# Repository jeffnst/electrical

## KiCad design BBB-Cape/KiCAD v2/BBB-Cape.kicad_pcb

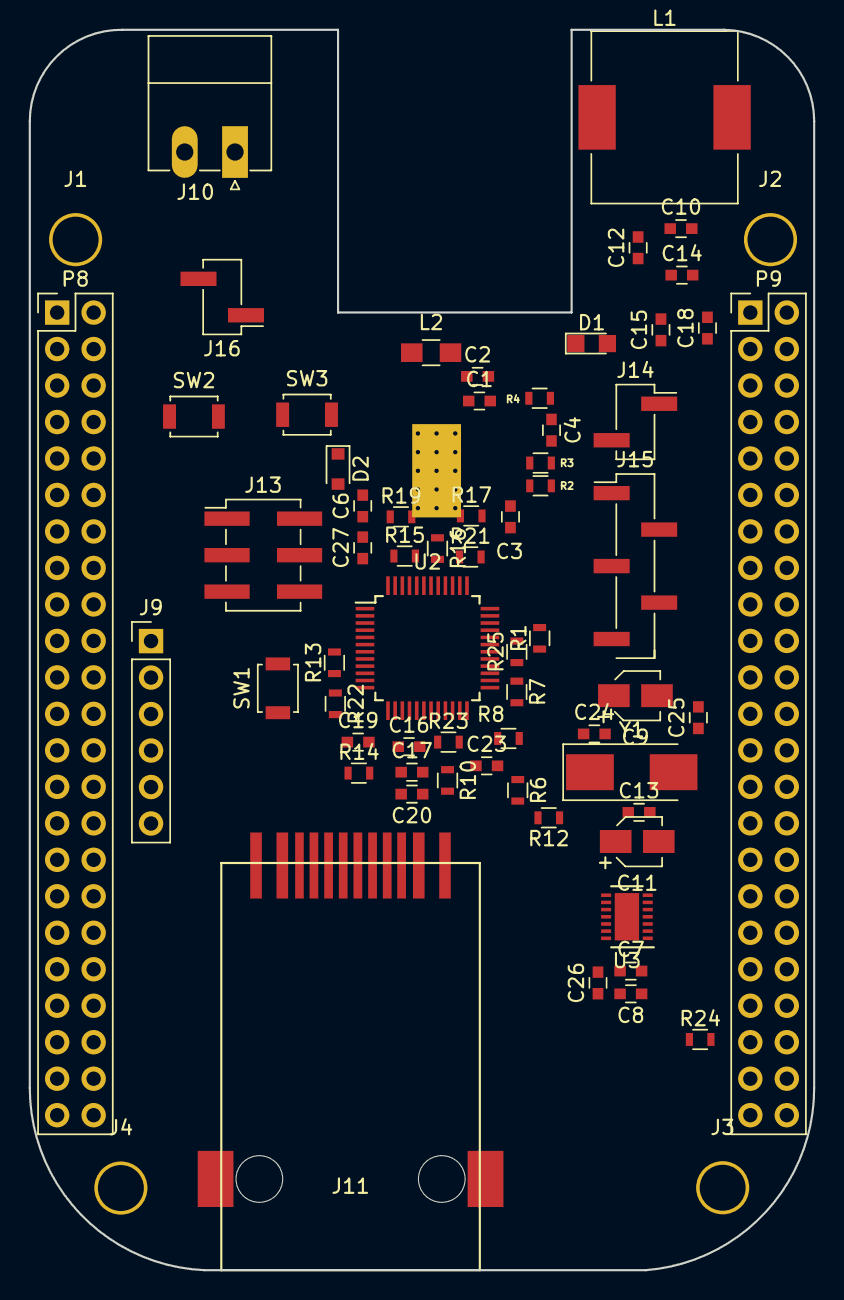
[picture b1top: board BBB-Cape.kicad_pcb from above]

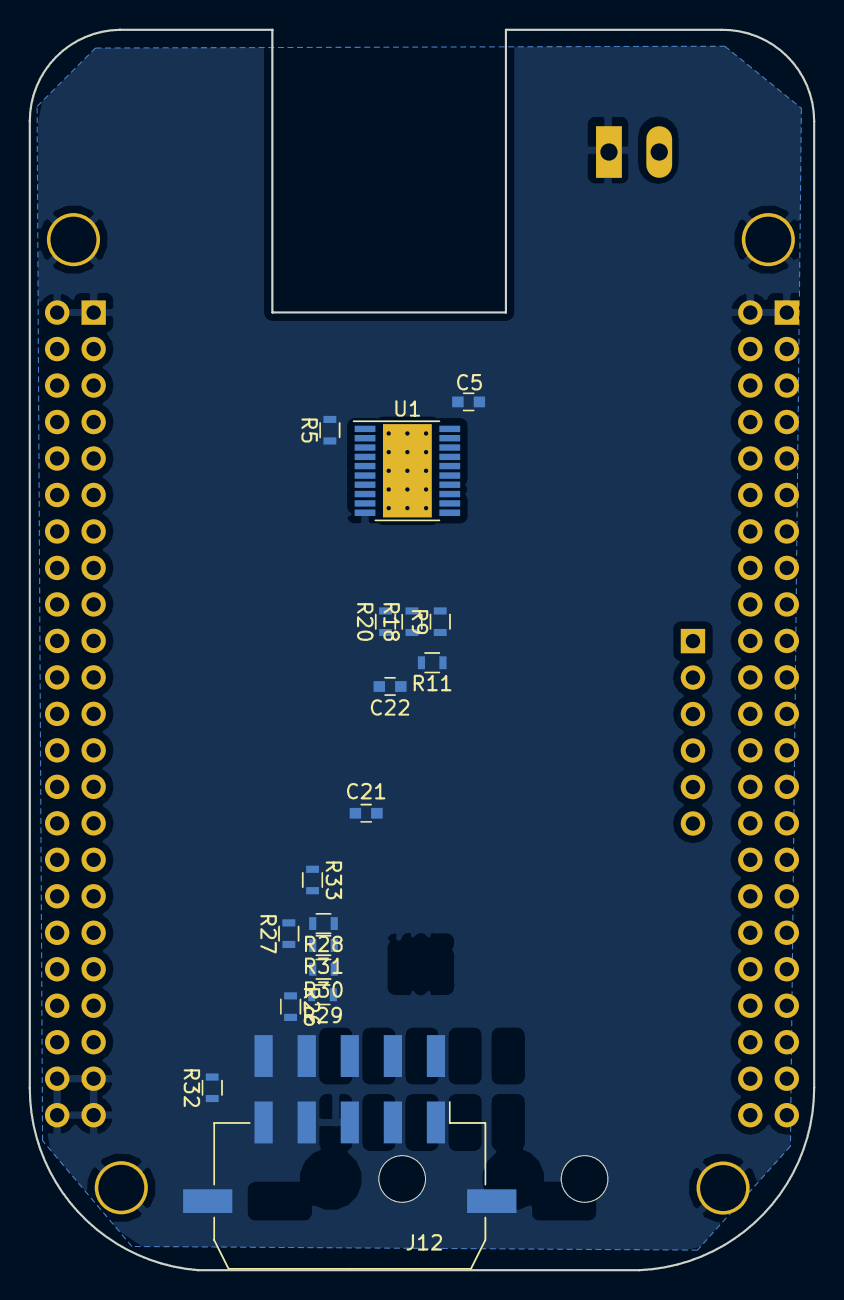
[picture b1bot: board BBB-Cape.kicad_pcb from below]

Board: 2 copper layers, 54.6 x 86.4 mm, 85 parts (18 on the bottom side), 75 nets, no tracks yet.

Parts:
C1: 1.00uF; C_0603
C2, C10, C12, C13, C14, C15, C18, C19, C26, C27: 0.1uF; C_0603
C3: 270pF; C_0603
C4: 1.80nF; C_0603
C5, C21: 22nF; C_0603
C6: 8.2nF; C_0603
C7, C8: 47uF; C_0603
C9, C11: 10uF; CP_Elec_3x5.3
C16, C17: 6.8nF; C_0603
C20, C23: 10nF; C_0603
C22: 4.7uF; C_0603
C24, C25: 18pF; C_0603
D1: LED; LED_0805
D2: 0.455V 20.0A; D_0805
J1, J2, J3, J4: MOUNTING_HOLE; MountingHole_3.2mm_M3_Pad
J9: 01x06_Stackable Header; Pin_Header_Straight_1x06_Pitch2.54mm
J10: Conn_01x02; PhoenixContact_MC-G_02x3.50mm_Angled
J11: RJ45-TRANSFO; RJ45_Surface_Mount
J12: DB9_Female; Molex_MicroFit_3.0-43045-1010_10x3.00mm_Angled
J13: SPI1; Pin_Header_Straight_2x03_Pitch2.54mm_SMD
J14: I2C2; Pin_Header_Straight_1x02_Pitch2.54mm_SMD_Pin1Right
J15: UART5; Pin_Header_Straight_1x05_Pitch2.54mm_SMD_Pin1Left
J16: 5V PWR; Pin_Header_Straight_1x02_Pitch2.54mm_SMD_Pin1Left
L1: 27.0uH; L_Wuerth_HCM-1240
L2: BLM21PG121SN1D; L_0805_HandSoldering
P8, P9: 02x23_Stackable Header; Pin_Header_Straight_2x23_Pitch2.54mm
R1, R7, R8: 330; R_0603
R2: 16.2k; R_0603
R3: 22.1k; R_0603
R4: 3.09k; R_0603
R5: 1.02k; R_0603
R6, R9: 49.9; R_0603
R10, R11: 82; R_0603
R12: 10; R_0603
R13: 12.4k; R_0603
R14, R15, R16, R17, R18, R19, R20, R21, R22, R23, R24: 10k; R_0603
R25: 10M; R_0603
R26, R27: 20k; R_0603
R28, R29, R30, R31: 0; R_0603
R32, R33: 120; R_0603
SW1: W5500_RST; SW_SPST_B3U-1000P
SW2: SYS_RST; SW_SPST_B3U-1000P
SW3: Power; SW_SPST_B3U-1000P
U1: LM25576MH; HTSSOP-20-1EP_4.4x6.5mm_Pitch0.65mm_ThermalPad
U2: WIZnet W5500; LQFP-48_7x7mm_Pitch0.5mm
U3: MAX13433EETD; DFN-14-1EP_3x4mm_Pitch0.5mm
Y1: 25MHz; Crystal_SMD_0603-2pin_6.0x3.5mm_HandSoldering

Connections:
3V3D: C11.1, C13.1, L2.2, R24.1, U2.28
ACT_LED: R7.1, U2.27
DGND: C1.2, C2.2, C3.2, C6.2, C8.2, C9.2, C10.2, C12.2, C14.2, C15.2, C18.2, C19.2, C20.2, C21.2, C22.2, C23.2, C24.2, C25.2, C26.1, C27.1, J1.1, J2.1, J3.1, J4.1, J10.1, J12.5, J13.6, J15.5, J16.2, P8.1, P8.2, P9.1, P9.2, P9.43, P9.44, P9.45, P9.46, R1.2, R2.1, R5.1, R13.2, R17.1, R18.1, R19.1, R20.1, R21.1, R23.1, R26.1, SW1.2, SW2.2, SW3.2, U1.10, U1.13, U1.14, U2.3, U2.9, U2.14, U2.16, U2.19, U2.29, U2.48, U3.6, U3.8, U3.15
EHRPWM2A: P8.19, P8.45
EHRPWM2B: P8.13, P8.46
I2C1_SCL/SPI0_CS0: P9.17, U2.32
I2C1_SCL/UART1_TXD: P9.24, R30.2
I2C1_SDA/SPI0_DI: P9.18, U2.34
I2C1_SDA/UART1_RXD: P9.26, R28.2
I2C2_SCL/SPI0_DO/UART2_TXD: P9.21, U2.35
I2C2_SCL/SPI1_CS1/UART1_RTSn: J14.1, P9.19
I2C2_SDA/SPI1_CS0/UART1_CTSn: J14.2, P9.20
I2C2_SDA/SPIO_SCLK/UART2_RXD: P9.22, U2.33
LINK_LED: R8.1, U2.25
unnamed: C1.1, J10.2, U1.3, U1.4
unnamed: C2.1, U1.1
unnamed: C3.1, U1.9
unnamed: C4.1, R4.1, R5.2, U1.7
unnamed: C4.2, R3.2
unnamed: C5.1, D2.1, L1.1, U1.17, U1.18, U1.19
unnamed: C5.2, U1.20
unnamed: C6.1, U1.11
unnamed: C7.2, C8.1
unnamed: C11.2, C13.2
unnamed: C16.1, J11.4
unnamed: C17.1, J11.6
unnamed: C20.1, J11.5, R10.2, R11.2
unnamed: C21.1, J11.2, R12.2
unnamed: C22.1, U2.20
unnamed: C23.1, U2.22
unnamed: C24.1, R25.1, U2.30, Y1.1
unnamed: C25.1, R25.2, U2.31, Y1.2
unnamed: D1.1, R1.1
unnamed: D2.2, U1.15, U1.16
unnamed: R2.2, U1.8
unnamed: R3.1, U1.6
unnamed: R13.1, U2.10
unnamed: R14.2, U2.45
unnamed: R15.2, U2.44
unnamed: R16.2, U2.43
unnamed: R17.2, U2.42
unnamed: R18.2, U2.41
unnamed: R19.2, U2.40
unnamed: R20.2, U2.39
unnamed: R21.2, U2.38
unnamed: R23.2, U2.23
unnamed: R28.1, U3.2
unnamed: R29.1, U3.4
unnamed: R30.1, U3.5
unnamed: R31.1, U3.3
PWR_BUT: P9.9, SW3.1
RS485_BBB_DE: R27.1, R31.2
RS485_BBB_RE: R26.2, R29.2
RS485_RX+: J12.3, R32.2, U3.11
RS485_RX-: J12.4, R32.1, U3.12
RS485_TX+: J12.2, R33.2, U3.10
RS485_TX-: J12.1, R33.1, U3.9
RX+: C16.2, R11.1, U2.6
RX-: C17.2, R10.1, U2.5
SPI1_CS0: J13.2, P9.28
SPI1_D0: J13.3, P9.29
SPI1_DI: J13.4, P9.30
SPI1_SCLK: J13.5, P9.31
SYS_5V: P9.7, P9.8
SYS_RESETn: P9.10, SW2.1
TX+: J11.1, R6.2, U2.2
TX-: J11.3, R9.2, U2.1
UART5_CTSn+: J15.3, P8.31
UART5_RTSn: J15.4, P8.32
UART5_RXD+: J15.1, P8.38
UART5_TXD+: J15.2, P8.37
VDD_3V3: C9.1, C10.1, C12.1, C14.1, C15.1, C18.1, C19.1, D1.2, J13.1, L2.1, P9.3, P9.4, R6.1, R9.1, R12.1, R14.1, R15.1, R16.1, R22.1, U2.4, U2.8, U2.11, U2.15, U2.17, U2.21
VDD_5V: C7.1, C26.2, C27.2, J16.1, L1.2, P9.5, P9.6, R4.2, R27.2, U1.12, U3.1, U3.14
W5500_INT: P9.41, R24.2, U2.36
W5500_RST: R22.2, SW1.1, U2.37

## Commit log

2018-01-09 BBB for review
2018-01-10 Cape Routing Fixes
    General cleanup and optimization.
2018-01-10 Rev3 started, commit for mark to work on schematic
2018-01-11 Schematic Rework for Rev3
    Updated schematic based on Ed changes / review.
2018-01-11 Layout start for Rev3
2018-01-15 Schematic Update
    Updated pin mapping as described by Ed.
2018-01-15 Layout Update
    Changed RJ45 connector to a surface mount component. Need to properly reposition P8 and P9.
2018-01-15 Layout Fix
    Updated a few footprints, fixed the positioning of P8 and P9, and adjusted general layout a bit.
2018-02-02 Layout Update
    Initial resistor placement. Fixed ethernet connector and RS485 connector position.
2018-02-04 Connector Position Changes
    Moved around the ethernet and RS485 connectors so they will not interfere with the BBB.
